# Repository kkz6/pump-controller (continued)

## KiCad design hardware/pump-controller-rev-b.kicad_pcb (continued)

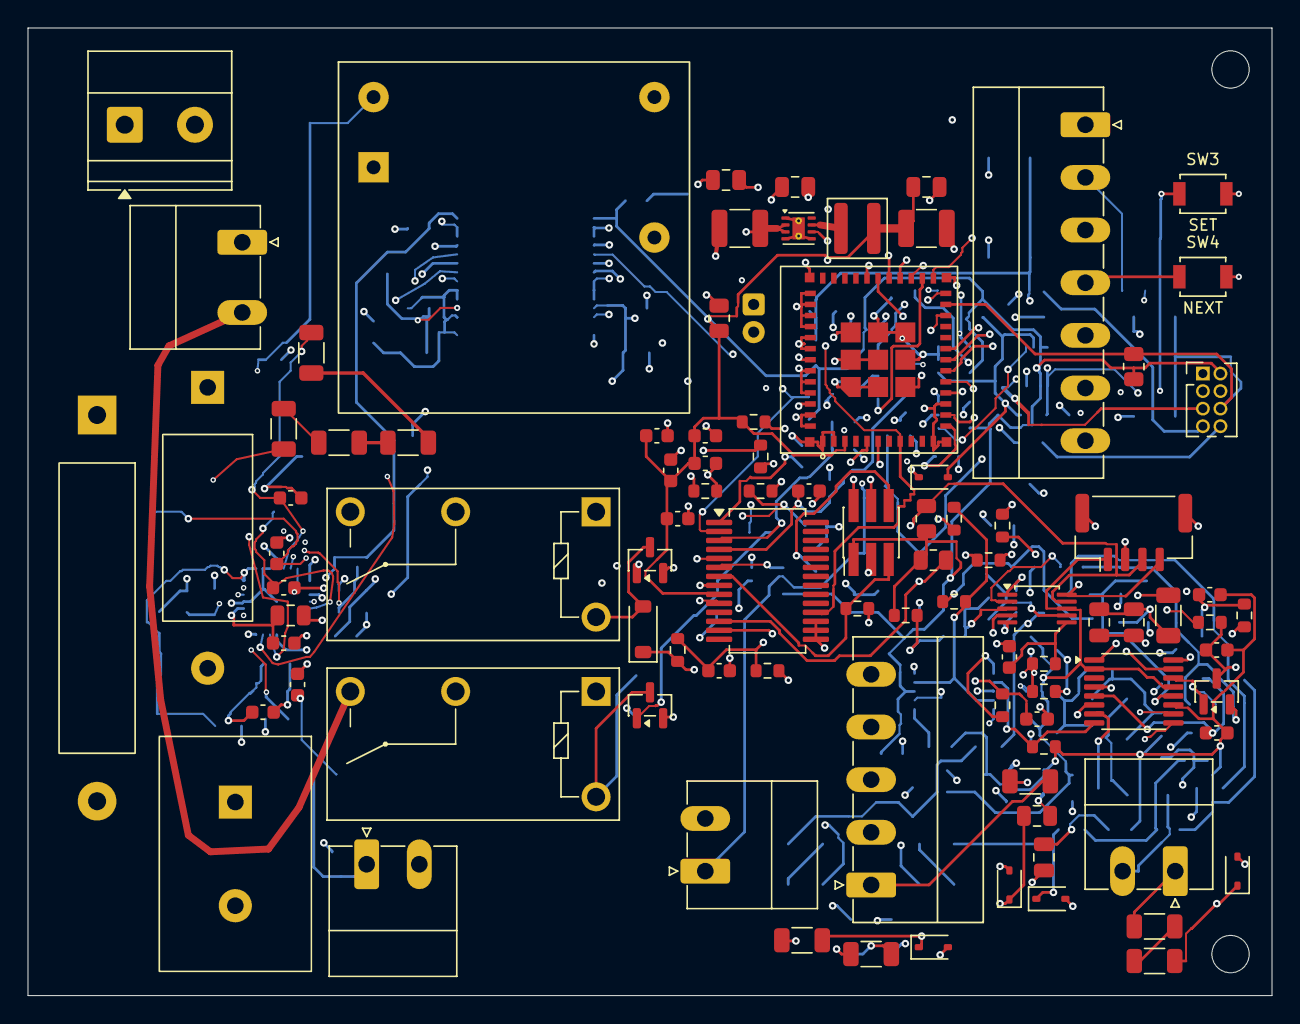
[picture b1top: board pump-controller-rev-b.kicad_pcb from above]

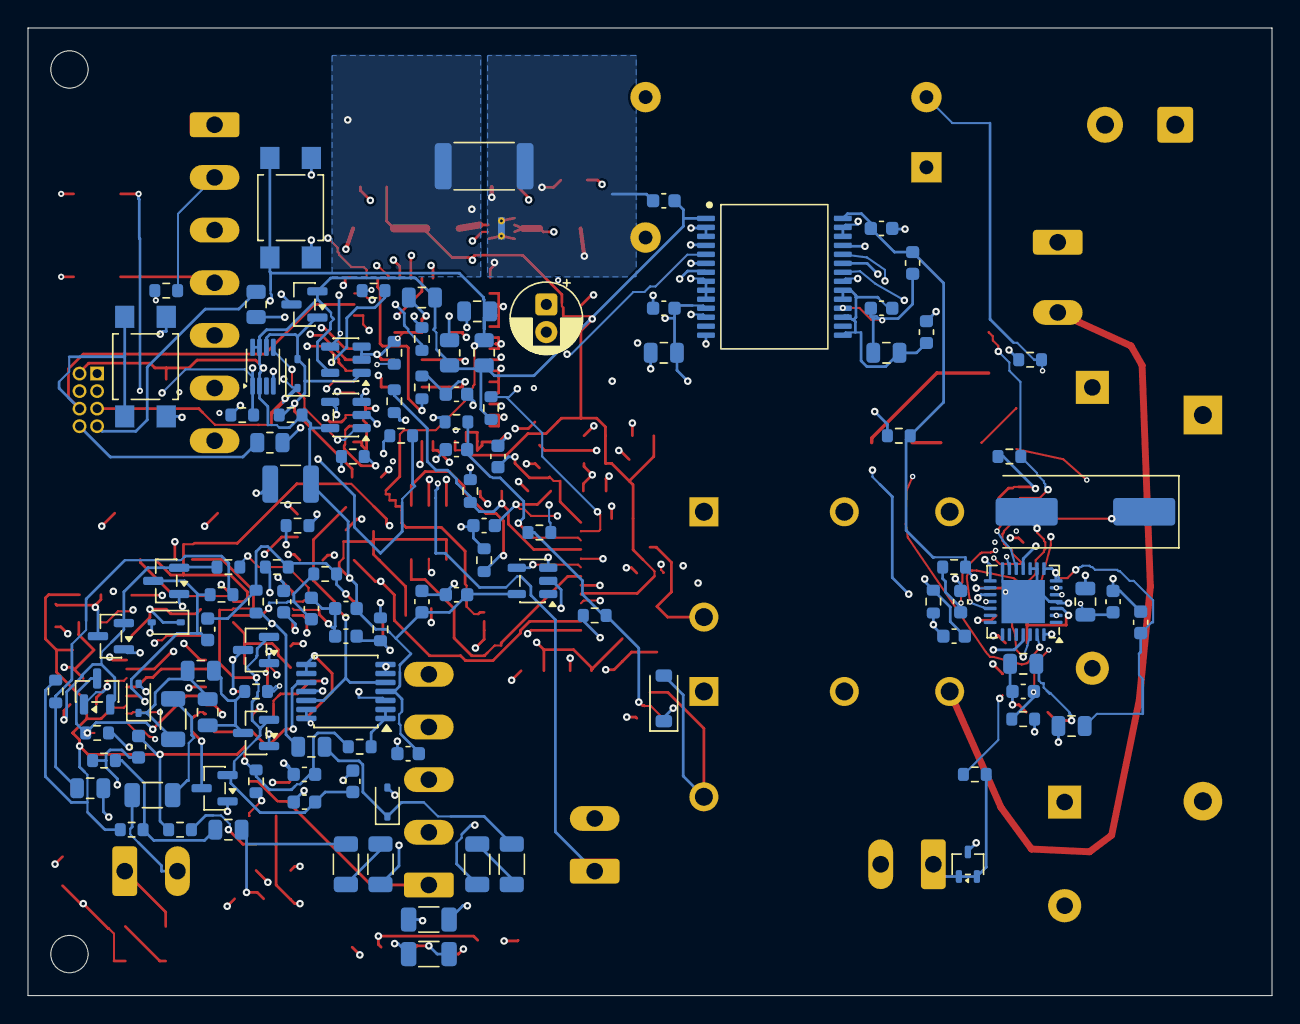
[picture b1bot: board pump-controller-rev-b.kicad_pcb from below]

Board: 4 copper layers, 90.0 x 70.0 mm, 210 parts (115 on the bottom side), 123 nets.

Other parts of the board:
H1, H2: MountingHole_2.7mm_M2.5

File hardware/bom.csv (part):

Reference,Value,MPN,Description,Footprint,Datasheet,Sheet,DNP
J1,AC INPUT L/N,1715721,Phoenix MKDS 1.5/2-5.08 2-way input connector; 400 V rated under III/2,"TerminalBlock_Phoenix:TerminalBlock_Phoenix_MKDS-1,5-2-5.08_1x02_P5.08mm_Horizontal",https://www.phoenixcontact.com/en-us/products/printed-circui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,power,False
F1,T1A 600VAC,0ADKP1000-RE,Bel 1 A time-delay axial pigtail fuse; 200 A interrupting capacity at 600 VAC per TUV; coordinate with upstream protection,Pump:Fuse_Axial_5x20_P27.94,https://www.belfuse.com/media/datasheets/products/circuit-pr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,power,False
R1,22R 3W FUSIBLE,AC03000002209JACCS,Vishay AC03-CS 22 ohm 3 W 5% fusible safety resistor; keep heat away from MCU and capacitors,Pump:R_Axial_L13_D6_P20.32,https://www.vishay.com/docs/28909/acxxcs.pdf,power,False
RV1,TMOV 320VAC,TMOV14RP320EL2B7,"Thermally protected 14 mm MOV, 320 VAC continuous; INLINE crimped L2B7 lead option required for footprint; surge coordination unverified",Pump:TMOV14_Inline_P7.5,https://www.littelfuse.com/assetdocs/tmov-itmov?assetguid=bd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,power,False
U1,5V 1.2A ISOLATED,RACM06E-05SK/277,"6 W reinforced-isolation AC/DC module, 25.4 x 25.4 x 16.7 mm; 5 V model delivers 6 W to 50 C at 115-277 VAC; keep output floating",Pump:RACM06E,https://recom-power.com/pdf/Powerline_AC-DC/RACM06E-K_277.pdf,power,False
C1,47uF 16V 105C,Generic 47uF 16V 105C low-impedance electrolytic D5 P2.0,5 V bulk reservoir near relay branch; select <=5 mm diameter and <=11 mm height,Capacitor_THT:CP_Radial_D5.0mm_P2.00mm,,power,False
C2,100nF 50V X7R,Generic 100nF 50V X7R 0805,Local ceramic bypass; X7R dielectric; verify effective capacitance at bias,Capacitor_SMD:C_0805_2012Metric,,power,False
C3,22uF 16V X7R,Generic 22uF 16V X7R 1210,Buck input capacitor directly at VIN/PGND; 22 uF nominal chosen to retain at least 10 uF effective at 5 V including bias/tolerance; qualify purchased part,Capacitor_SMD:C_1210_3225Metric,,power,False
C4,100nF 50V X7R,Generic 100nF 50V X7R 0805,Buck high-frequency input bypass directly at VIN/PGND,Capacitor_SMD:C_0805_2012Metric,,power,False
U2,TPS62162 3V3 1A,TPS62162DSGR,"Fixed 3.3 V synchronous buck; FB tied to AGND, VOS Kelvin-connected to output capacitor; EP to ground with thermal vias",Package_SON:Texas_DSG0008A_WSON-8-1EP_2x2mm_P0.5mm_EP0.9x1.6mm_ThermalVias,https://www.ti.com/lit/ds/symlink/tps62160.pdf,power,False
L1,2.2uH,74438357022,"Wuerth WE-MAPI 4030; 4.1x4.1x3.1 mm, 2.2 uH, 4.6 A saturation at 10% drop, max 26 mOhm DCR",Inductor_SMD:L_Wuerth_MAPI-4030,https://www.we-online.com/components/products/datasheet/7443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,power,False
C5,22uF 10V X7R,Generic 22uF 10V X7R 1210,Buck output capacitor at L1/VOS; select effective capacitance within TI datasheet recommended range after bias/tolerance,Capacitor_SMD:C_1210_3225Metric,,power,False
C6,100nF 50V X7R,Generic 100nF 50V X7R 0805,Local 3.3 V rail bypass,Capacitor_SMD:C_0805_2012Metric,,power,False
R2,33R 1% 2W MINIMUM LOAD,CRM2512-FX-33R0ELF,"Bourns 2512 thick-film 33 ohm 1%, 2 W at 70 C with 300 mm2 combined solder-pad/trace copper per datasheet; permanent 5 V minimum-load resistor, 0.677-0.844 W at 4.75-5.25 V including 1% tolerance. Reserve copper area and keep away from probes, precision meter components, antenna module and electrolytics. Revised module local ambient limit 50 C.",Resistor_SMD:R_2512_6332Metric,https://www.bourns.com/docs/product-datasheets/crm.pdf,power,False
U3,ESP32-C6-MINI-1U-H8,ESP32-C6-MINI-1U-H8,8 MB flash; external antenna; hardware supports Matter over Wi-Fi or Thread. Antenna must be outside metal starter enclosure. GPIO17 drives ARM_CMD interlock rearm; GPIO16 UART TX logs only; GPIO4/5/15 unused; strap levels preserved.,Pump:ESP32-C6-MINI-1U,https://documentation.espressif.com/esp32-c6-mini-1_mini-1u_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,mcu,False
C20,22uF 10V X7R,Generic 22uF 10V X7R 1210,Module bulk capacitor adjacent to pin 3; effective capacitance >=10 uF at 3.3 V,Capacitor_SMD:C_1210_3225Metric,,mcu,False
C21,100nF 50V X7R,Generic 100nF 50V X7R 0805,Module bypass immediately at pin 3 and ground pads,Capacitor_SMD:C_0805_2012Metric,,mcu,False
C22,1uF 10V X7R,Generic 1uF 10V X7R 0805,Enable RC delay with R20; watchdog/supervisor uses open-drain reset only,Capacitor_SMD:C_0805_2012Metric,,mcu,False
R20,10k,Generic 10k 1% 0.125 W 0805,Module EN pull-up; 10 ms nominal RC with C22,Resistor_SMD:R_0805_2012Metric,,mcu,False
R21,10k,Generic 10k 1% 0.125 W 0805,GPIO9 boot strap pull-up; SW2 pulls low for UART/USB download,Resistor_SMD:R_0805_2012Metric,,mcu,False
R22,10k,Generic 10k 1% 0.125 W 0805,GPIO8 must be high while GPIO9 is low to enter serial download mode,Resistor_SMD:R_0805_2012Metric,,mcu,False
R24,3.3k,Generic 3.3k 1% 0.125 W 0805,I2C SDA pull-up; populate one pull-up set on assembled controller,Resistor_SMD:R_0805_2012Metric,,mcu,False
R25,3.3k,Generic 3.3k 1% 0.125 W 0805,I2C SCL pull-up; verify bus capacitance/rise time at selected clock,Resistor_SMD:R_0805_2012Metric,,mcu,False
R26,10k,Generic 10k 1% 0.125 W 0805,Keep metering IC deselected while ESP32 is resetting,Resistor_SMD:R_0805_2012Metric,,mcu,False
R27,22R,Generic 22R 1% 0.125 W 0805,Optional internal USB service path; series resistor adjacent to module,Resistor_SMD:R_0805_2012Metric,,mcu,False
R28,22R,Generic 22R 1% 0.125 W 0805,Optional internal USB service path; route D+/D- as 90-ohm differential pair,Resistor_SMD:R_0805_2012Metric,,mcu,False
SW1,TACT NO,TL3305AF160QG,Momentary reset button; footprint groups two physically common terminals as each logical pad,Button_Switch_SMD:SW_SPST_TL3305A,https://www.e-switch.com/wp-content/uploads/2023/01/TL3305.pdf,mcu,False
SW2,TACT NO,TL3305AF160QG,Momentary boot/download button; hold low during reset for download,Button_Switch_SMD:SW_SPST_TL3305A,https://www.e-switch.com/wp-content/uploads/2023/01/TL3305.pdf,mcu,False
J2,SERVICE 2x4 1.27mm,Generic 2x4 1.27 mm vertical male header,"Internal service header; pin 4 is ARM_TEST/ARM_CMD, NOT UART RX; native USB is the programming interface: 3.3 V pin is voltage reference only. No VBUS. Service only with mains disconnected and an isolated 5 V bench supply; do not back-power via 3V3 or signal pins.",Connector_PinHeader_1.27mm:PinHeader_2x04_P1.27mm_Vertical,,mcu,False
U10,ADE7953ACPZ,ADE7953ACPZ,Single phase metering IC; poll registers through SPI at 1MHz,Package_CSP:LFCSP-28-1EP_5x5mm_P0.5mm_EP3.14x3.14mm,https://www.analog.com/media/en/technical-documentation/data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,meter_ic,False
C40,4.7uF,"SPEC: 4.7uF X7R, 10%, 16V","X7R, 10%, 16V",Capacitor_SMD:C_0805_2012Metric,,meter_ic,False
C41,100nF,"SPEC: 100nF X7R, 10%, 16V","X7R, 10%, 16V",Capacitor_SMD:C_0603_1608Metric,,meter_ic,False
C42,4.7uF,"SPEC: 4.7uF X7R, 10%, 16V","X7R, 10%, 16V",Capacitor_SMD:C_0805_2012Metric,,meter_ic,False
C43,100nF,"SPEC: 100nF X7R, 10%, 16V","X7R, 10%, 16V",Capacitor_SMD:C_0603_1608Metric,,meter_ic,False
C44,4.7uF,"SPEC: 4.7uF X7R, 10%, 16V","X7R, 10%, 16V",Capacitor_SMD:C_0805_2012Metric,,meter_ic,False
C45,100nF,"SPEC: 100nF X7R, 10%, 16V","X7R, 10%, 16V",Capacitor_SMD:C_0603_1608Metric,,meter_ic,False
C46,10uF,"SPEC: 10uF X7R, 10%, 16V","X7R, 10%, 16V",Capacitor_SMD:C_0805_2012Metric,,meter_ic,False
C47,100nF,"SPEC: 100nF X7R, 10%, 16V","X7R, 10%, 16V",Capacitor_SMD:C_0603_1608Metric,,meter_ic,False
R40,10k,"SPEC: 10k 1%, 0.1W, 0603","1%, 0.1W, 0603",Resistor_SMD:R_0603_1608Metric,,meter_ic,False
C48,1uF,"SPEC: 1uF X7R, 10%, 16V","X7R, 10%, 16V",Capacitor_SMD:C_0603_1608Metric,,meter_ic,False
R41,10k,"SPEC: 10k 1%, 0.1W, 0603","1%, 0.1W, 0603",Resistor_SMD:R_0603_1608Metric,,meter_ic,False
Y1,3.579545MHz / CL18pF,ABLS-3.579545MHZ-B2-T,18pF load; 27pF caps assume 4.5pF total stray; confirm oscillator start/accuracy,Crystal:Crystal_SMD_HC49-SD,https://abracon.com/Resonators/ABLS.pdf,meter_ic,False
C49,27pF,"SPEC: 27pF C0G, 5%, 50V","C0G, 5%, 50V",Capacitor_SMD:C_0603_1608Metric,,meter_ic,False
C50,27pF,"SPEC: 27pF C0G, 5%, 50V","C0G, 5%, 50V",Capacitor_SMD:C_0603_1608Metric,,meter_ic,False
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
